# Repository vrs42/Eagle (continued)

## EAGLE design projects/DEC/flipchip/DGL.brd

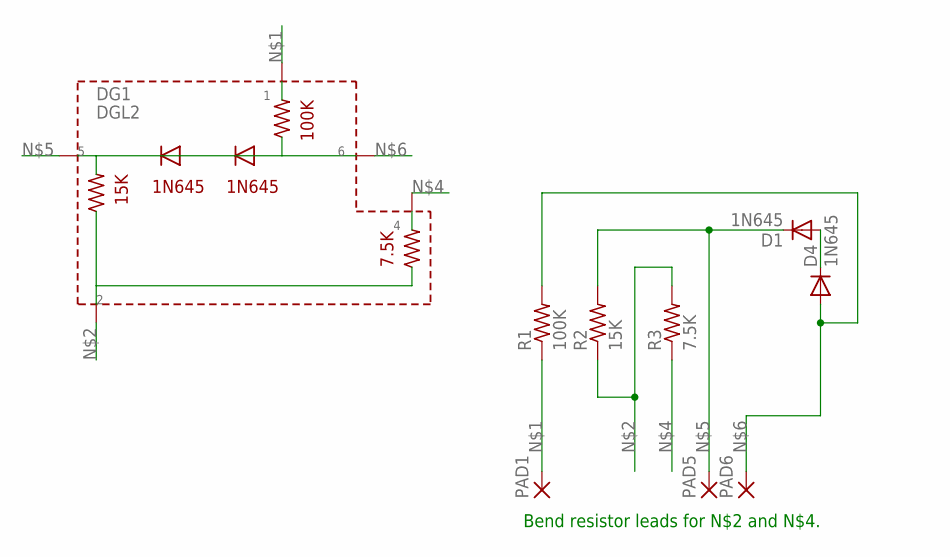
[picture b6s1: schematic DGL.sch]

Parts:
D1, D4: 1N645; DO34-7
DG1: DGL2
PAD1, PAD5, PAD6: 1,6/0,8
R1: 100K; 0207/7
R2: 15K; 0207/7
R3: 7.5K; 0207/7

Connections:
unnamed: DG1.P$1 (1), PAD1.1, R1.1
unnamed: DG1.P$2 (2), R2.1, R3.2
unnamed: DG1.P$4 (4), R3.1
unnamed: D1.C, DG1.P$5 (5), PAD5.1, R2.2
unnamed: D4.A, DG1.P$6 (6), PAD6.1, R1.2
unnamed: D1.A, D4.C

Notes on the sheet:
Bend resistor leads for N$2 and N$4.

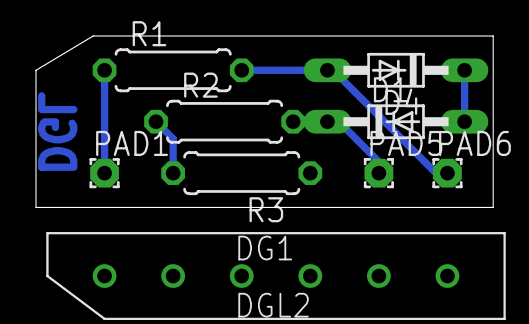
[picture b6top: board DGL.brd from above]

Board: 2 copper layers, 25.4 x 9.5 mm, 9 parts (0 on the bottom side), 6 nets.
